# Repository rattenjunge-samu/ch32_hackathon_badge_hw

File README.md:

# ch32_hackathon_badge_hw

This repo contains all hardware files needed to produce the 2025 hackathon badge.

## Programming

Attach a minichlink with +, - and SWIO to the pin header

## Revision A

This is the initially produced pcb marked on the back with serial numbers from #00 up to #36.

It needs to be run on two button cells stacked on each other ( = in series)

## Revision B

Not yet produced.

Bugfixes:

- improved layout to hopefully work on a single button cell
  - big thank you to [prozessorkern](https://github.com/prozessorkern/)

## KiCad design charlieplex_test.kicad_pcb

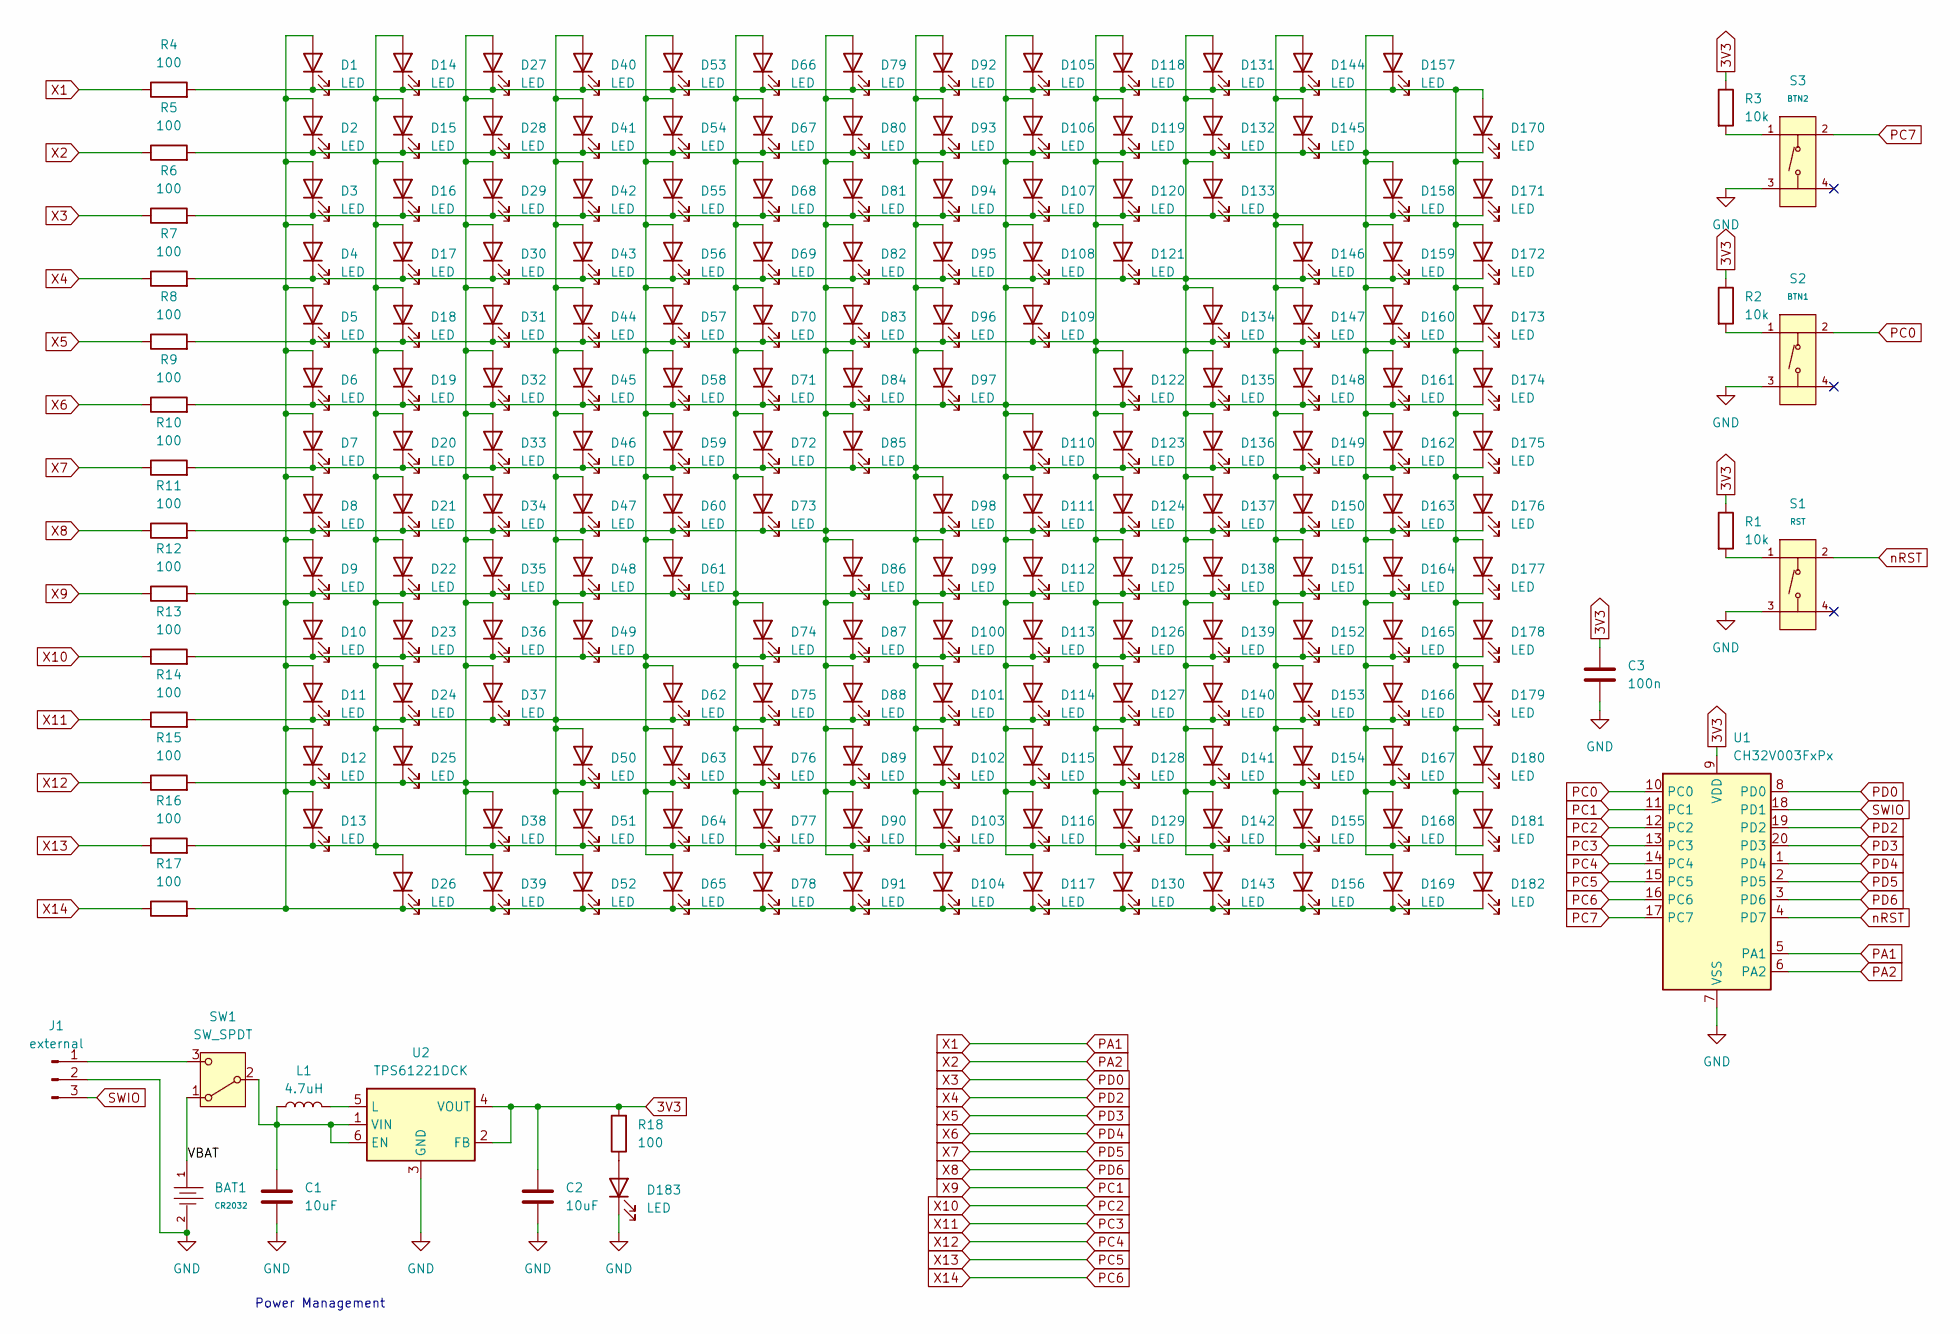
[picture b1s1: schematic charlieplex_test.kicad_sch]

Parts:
BAT1: CR2032; BAT-TH_BS-07-A1BJ001; Part BS-07-A1BJ001; LCSC C2979167
C1, C2: 10uF; C_0805
C3: 100n; C_0603_1608Metric
D1, D2, D3, D4, D5, D6, D7, D8, D9, D10, D11, D12, D13, D14, D15, D16, D17, D18, D19, D20, D21, D22, D23, D24, D25, D26, D27, D28, D29, D30, D31, D32, D33, D34, D35, D36, D37, D38, D39, D40, D41, D42, D43, D44, D45, D46, D47, D48, D49, D50, D51, D52, D53, D54, D55, D56, D57, D58, D59, D60, D61, D62, D63, D64, D65, D66, D67, D68, D69, D70, D71, D72, D73, D74, D75, D76, D77, D78, D79, D80, D81, D82, D83, D84, D85, D86, D87, D88, D89, D90, D91, D92, D93, D94, D95, D96, D97, D98, D99, D100, D101, D102, D103, D104, D105, D106, D107, D108, D109, D110, D111, D112, D113, D114, D115, D116, D117, D118, D119, D120, D121, D122, D123, D124, D125, D126, D127, D128, D129, D130, D131, D132, D133, D134, D135, D136, D137, D138, D139, D140, D141, D142, D143, D144, D145, D146, D147, D148, D149, D150, D151, D152, D153, D154, D155, D156, D157, D158, D159, D160, D161, D162, D163, D164, D165, D166, D167, D168, D169, D170, D171, D172, D173, D174, D175, D176, D177, D178, D179, D180, D181, D182, D183: LED; D_0603
J1: external; PinHeader_1x03_P2.54mm_Vertical
L1: 4.7uH; L_0805
R1, R2, R3: 10k; R_0805
R4, R5, R6, R7, R8, R9, R10, R11, R12, R13, R14, R15, R16, R17, R18: 100; R_0603
S1: RST; SW-SMD_4P-L5.1-W5.1-P3.70-LS6.5-TL-2; Voltage Rating (Dc) 12V; Part TS-1187A-B-A-B; LCSC C318884
S2: BTN1; SW-SMD_4P-L5.1-W5.1-P3.70-LS6.5-TL-2; Voltage Rating (Dc) 12V; Part TS-1187A-B-A-B; LCSC C318884
S3: BTN2; SW-SMD_4P-L5.1-W5.1-P3.70-LS6.5-TL-2; Voltage Rating (Dc) 12V; Part TS-1187A-B-A-B; LCSC C318884
SW1: SW_SPDT; SW_SPDT_PCM12
U1: CH32V003FxPx; TSSOP-20_4.4x6.5mm_P0.65mm
U2: TPS61221DCK; Texas_R-PDSO-G6

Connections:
3V3: C2.1, C3.1, R1.1, R2.1, R3.1, R18.2, U1.9 (VDD), U2.2 (FB), U2.4 (VOUT)
/VBAT: BAT1.1, SW1.1 (A)
GND: BAT1.2, C1.2, C2.2, C3.2, D183.1 (K), J1.2, S1.3 (C), S2.3 (C), S3.3 (C), U1.7 (VSS), U2.3 (GND)
unnamed: D1.2 (A), D2.2 (A), D3.2 (A), D4.2 (A), D5.2 (A), D6.2 (A), D7.2 (A), D8.2 (A), D9.2 (A), D10.2 (A), D11.2 (A), D12.2 (A), D13.2 (A), D26.1 (K), D39.1 (K), D52.1 (K), D65.1 (K), D78.1 (K), D91.1 (K), D104.1 (K), D117.1 (K), D130.1 (K), D143.1 (K), D156.1 (K), D169.1 (K), D182.1 (K), R17.2
unnamed: D1.1 (K), D14.1 (K), D27.1 (K), D40.1 (K), D53.1 (K), D66.1 (K), D79.1 (K), D92.1 (K), D105.1 (K), D118.1 (K), D131.1 (K), D144.1 (K), D157.1 (K), D170.2 (A), D171.2 (A), D172.2 (A), D173.2 (A), D174.2 (A), D175.2 (A), D176.2 (A), D177.2 (A), D178.2 (A), D179.2 (A), D180.2 (A), D181.2 (A), D182.2 (A), R4.2
unnamed: D10.1 (K), D23.1 (K), D36.1 (K), D49.1 (K), D53.2 (A), D54.2 (A), D55.2 (A), D56.2 (A), D57.2 (A), D58.2 (A), D59.2 (A), D60.2 (A), D61.2 (A), D62.2 (A), D63.2 (A), D64.2 (A), D65.2 (A), D74.1 (K), D87.1 (K), D100.1 (K), D113.1 (K), D126.1 (K), D139.1 (K), D152.1 (K), D165.1 (K), D178.1 (K), R13.2
unnamed: D7.1 (K), D20.1 (K), D33.1 (K), D46.1 (K), D59.1 (K), D72.1 (K), D85.1 (K), D92.2 (A), D93.2 (A), D94.2 (A), D95.2 (A), D96.2 (A), D97.2 (A), D98.2 (A), D99.2 (A), D100.2 (A), D101.2 (A), D102.2 (A), D103.2 (A), D104.2 (A), D110.1 (K), D123.1 (K), D136.1 (K), D149.1 (K), D162.1 (K), D175.1 (K), R10.2
unnamed: D11.1 (K), D24.1 (K), D37.1 (K), D40.2 (A), D41.2 (A), D42.2 (A), D43.2 (A), D44.2 (A), D45.2 (A), D46.2 (A), D47.2 (A), D48.2 (A), D49.2 (A), D50.2 (A), D51.2 (A), D52.2 (A), D62.1 (K), D75.1 (K), D88.1 (K), D101.1 (K), D114.1 (K), D127.1 (K), D140.1 (K), D153.1 (K), D166.1 (K), D179.1 (K), R14.2
unnamed: D12.1 (K), D25.1 (K), D27.2 (A), D28.2 (A), D29.2 (A), D30.2 (A), D31.2 (A), D32.2 (A), D33.2 (A), D34.2 (A), D35.2 (A), D36.2 (A), D37.2 (A), D38.2 (A), D39.2 (A), D50.1 (K), D63.1 (K), D76.1 (K), D89.1 (K), D102.1 (K), D115.1 (K), D128.1 (K), D141.1 (K), D154.1 (K), D167.1 (K), D180.1 (K), R15.2
unnamed: D13.1 (K), D14.2 (A), D15.2 (A), D16.2 (A), D17.2 (A), D18.2 (A), D19.2 (A), D20.2 (A), D21.2 (A), D22.2 (A), D23.2 (A), D24.2 (A), D25.2 (A), D26.2 (A), D38.1 (K), D51.1 (K), D64.1 (K), D77.1 (K), D90.1 (K), D103.1 (K), D116.1 (K), D129.1 (K), D142.1 (K), D155.1 (K), D168.1 (K), D181.1 (K), R16.2
unnamed: D6.1 (K), D19.1 (K), D32.1 (K), D45.1 (K), D58.1 (K), D71.1 (K), D84.1 (K), D97.1 (K), D105.2 (A), D106.2 (A), D107.2 (A), D108.2 (A), D109.2 (A), D110.2 (A), D111.2 (A), D112.2 (A), D113.2 (A), D114.2 (A), D115.2 (A), D116.2 (A), D117.2 (A), D122.1 (K), D135.1 (K), D148.1 (K), D161.1 (K), D174.1 (K), R9.2
unnamed: D2.1 (K), D15.1 (K), D28.1 (K), D41.1 (K), D54.1 (K), D67.1 (K), D80.1 (K), D93.1 (K), D106.1 (K), D119.1 (K), D132.1 (K), D145.1 (K), D157.2 (A), D158.2 (A), D159.2 (A), D160.2 (A), D161.2 (A), D162.2 (A), D163.2 (A), D164.2 (A), D165.2 (A), D166.2 (A), D167.2 (A), D168.2 (A), D169.2 (A), D170.1 (K), R5.2
unnamed: D3.1 (K), D16.1 (K), D29.1 (K), D42.1 (K), D55.1 (K), D68.1 (K), D81.1 (K), D94.1 (K), D107.1 (K), D120.1 (K), D133.1 (K), D144.2 (A), D145.2 (A), D146.2 (A), D147.2 (A), D148.2 (A), D149.2 (A), D150.2 (A), D151.2 (A), D152.2 (A), D153.2 (A), D154.2 (A), D155.2 (A), D156.2 (A), D158.1 (K), D171.1 (K), R6.2
unnamed: D4.1 (K), D17.1 (K), D30.1 (K), D43.1 (K), D56.1 (K), D69.1 (K), D82.1 (K), D95.1 (K), D108.1 (K), D121.1 (K), D131.2 (A), D132.2 (A), D133.2 (A), D134.2 (A), D135.2 (A), D136.2 (A), D137.2 (A), D138.2 (A), D139.2 (A), D140.2 (A), D141.2 (A), D142.2 (A), D143.2 (A), D146.1 (K), D159.1 (K), D172.1 (K), R7.2
unnamed: D5.1 (K), D18.1 (K), D31.1 (K), D44.1 (K), D57.1 (K), D70.1 (K), D83.1 (K), D96.1 (K), D109.1 (K), D118.2 (A), D119.2 (A), D120.2 (A), D121.2 (A), D122.2 (A), D123.2 (A), D124.2 (A), D125.2 (A), D126.2 (A), D127.2 (A), D128.2 (A), D129.2 (A), D130.2 (A), D134.1 (K), D147.1 (K), D160.1 (K), D173.1 (K), R8.2
unnamed: D8.1 (K), D21.1 (K), D34.1 (K), D47.1 (K), D60.1 (K), D73.1 (K), D79.2 (A), D80.2 (A), D81.2 (A), D82.2 (A), D83.2 (A), D84.2 (A), D85.2 (A), D86.2 (A), D87.2 (A), D88.2 (A), D89.2 (A), D90.2 (A), D91.2 (A), D98.1 (K), D111.1 (K), D124.1 (K), D137.1 (K), D150.1 (K), D163.1 (K), D176.1 (K), R11.2
unnamed: D9.1 (K), D22.1 (K), D35.1 (K), D48.1 (K), D61.1 (K), D66.2 (A), D67.2 (A), D68.2 (A), D69.2 (A), D70.2 (A), D71.2 (A), D72.2 (A), D73.2 (A), D74.2 (A), D75.2 (A), D76.2 (A), D77.2 (A), D78.2 (A), D86.1 (K), D99.1 (K), D112.1 (K), D125.1 (K), D138.1 (K), D151.1 (K), D164.1 (K), D177.1 (K), R12.2
unnamed: D183.2 (A), R18.1
unnamed: J1.1, SW1.3 (C)
unnamed: R1.2, S1.1 (A)
unnamed: R2.2, S2.1 (A)
unnamed: R3.2, S3.1 (A)
unnamed: C1.1, L1.1, SW1.2 (B), U2.1 (VIN), U2.6 (EN)
unnamed: L1.2, U2.5 (L)
PA1: R4.1, U1.5 (PA1)
PA2: R5.1, U1.6 (PA2)
PC0: S2.2 (B), U1.10 (PC0)
PC1: R12.1, U1.11 (PC1)
PC2: R13.1, U1.12 (PC2)
PC3: R14.1, U1.13 (PC3)
PC4: R15.1, U1.14 (PC4)
PC5: R16.1, U1.15 (PC5)
PC6: R17.1, U1.16 (PC6)
PC7: S3.2 (B), U1.17 (PC7)
PD0: R6.1, U1.8 (PD0)
PD2: R7.1, U1.19 (PD2)
PD3: R8.1, U1.20 (PD3)
PD4: R9.1, U1.1 (PD4)
PD5: R10.1, U1.2 (PD5)
PD6: R11.1, U1.3 (PD6)
SWIO: J1.3, U1.18 (PD1)
nRST: S1.2 (B), U1.4 (PD7)

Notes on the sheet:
Power Management

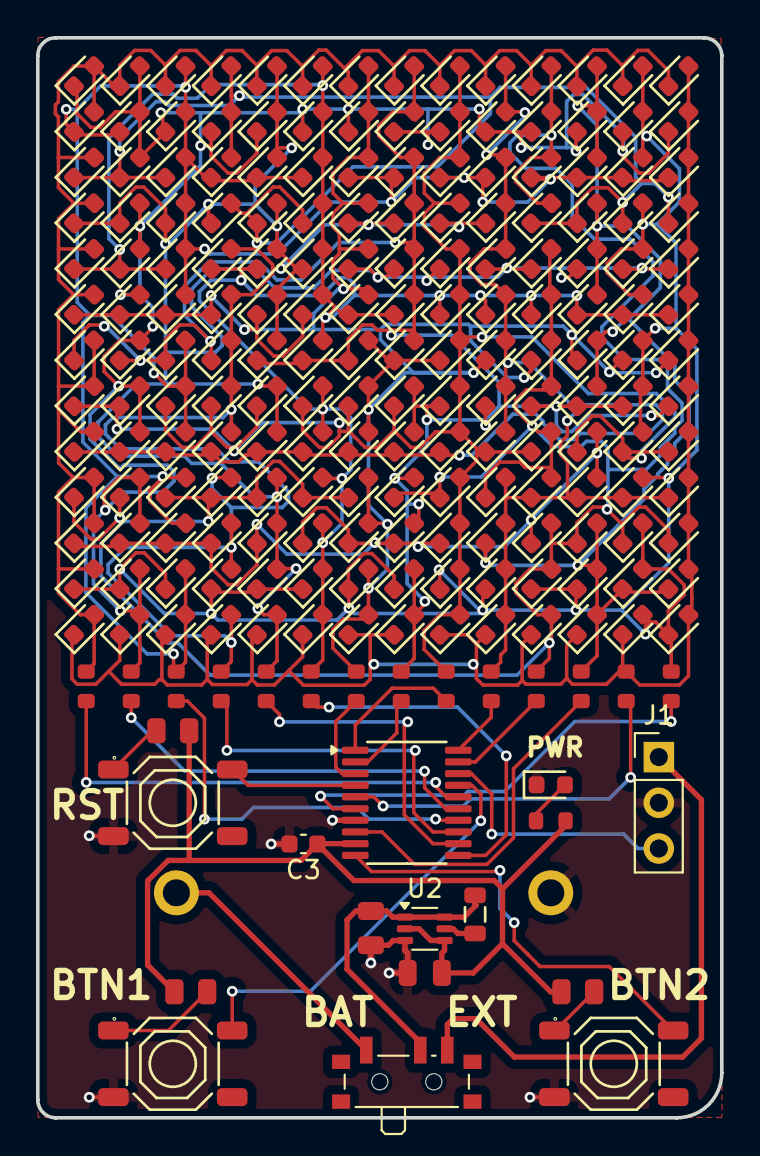
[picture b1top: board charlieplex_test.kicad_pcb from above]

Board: 2 copper layers, 38.0 x 60.0 mm, 213 parts (1 on the bottom side), 42 nets.

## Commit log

2025-01-16 init
2025-01-24 Improved layout of power supply actually work- added block capacitor to the uC as well as ground planes
2025-01-25 Rename schematic.pdf to schematic_rev_a.pdf
